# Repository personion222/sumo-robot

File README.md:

# sumo-robot
**Speedbump** - TEJ3MI sumo robot competition 2nd place winner.
- designed in OnShape and 3D printed
    <details>
    <summary>3D model screenshots</summary>

    </details><br>
- board designed in KiCad
    <details>
    <summary>schematic screenshots</summary>

    </details><br>
- powered by PIC16F15323 programmed with GCBasic script

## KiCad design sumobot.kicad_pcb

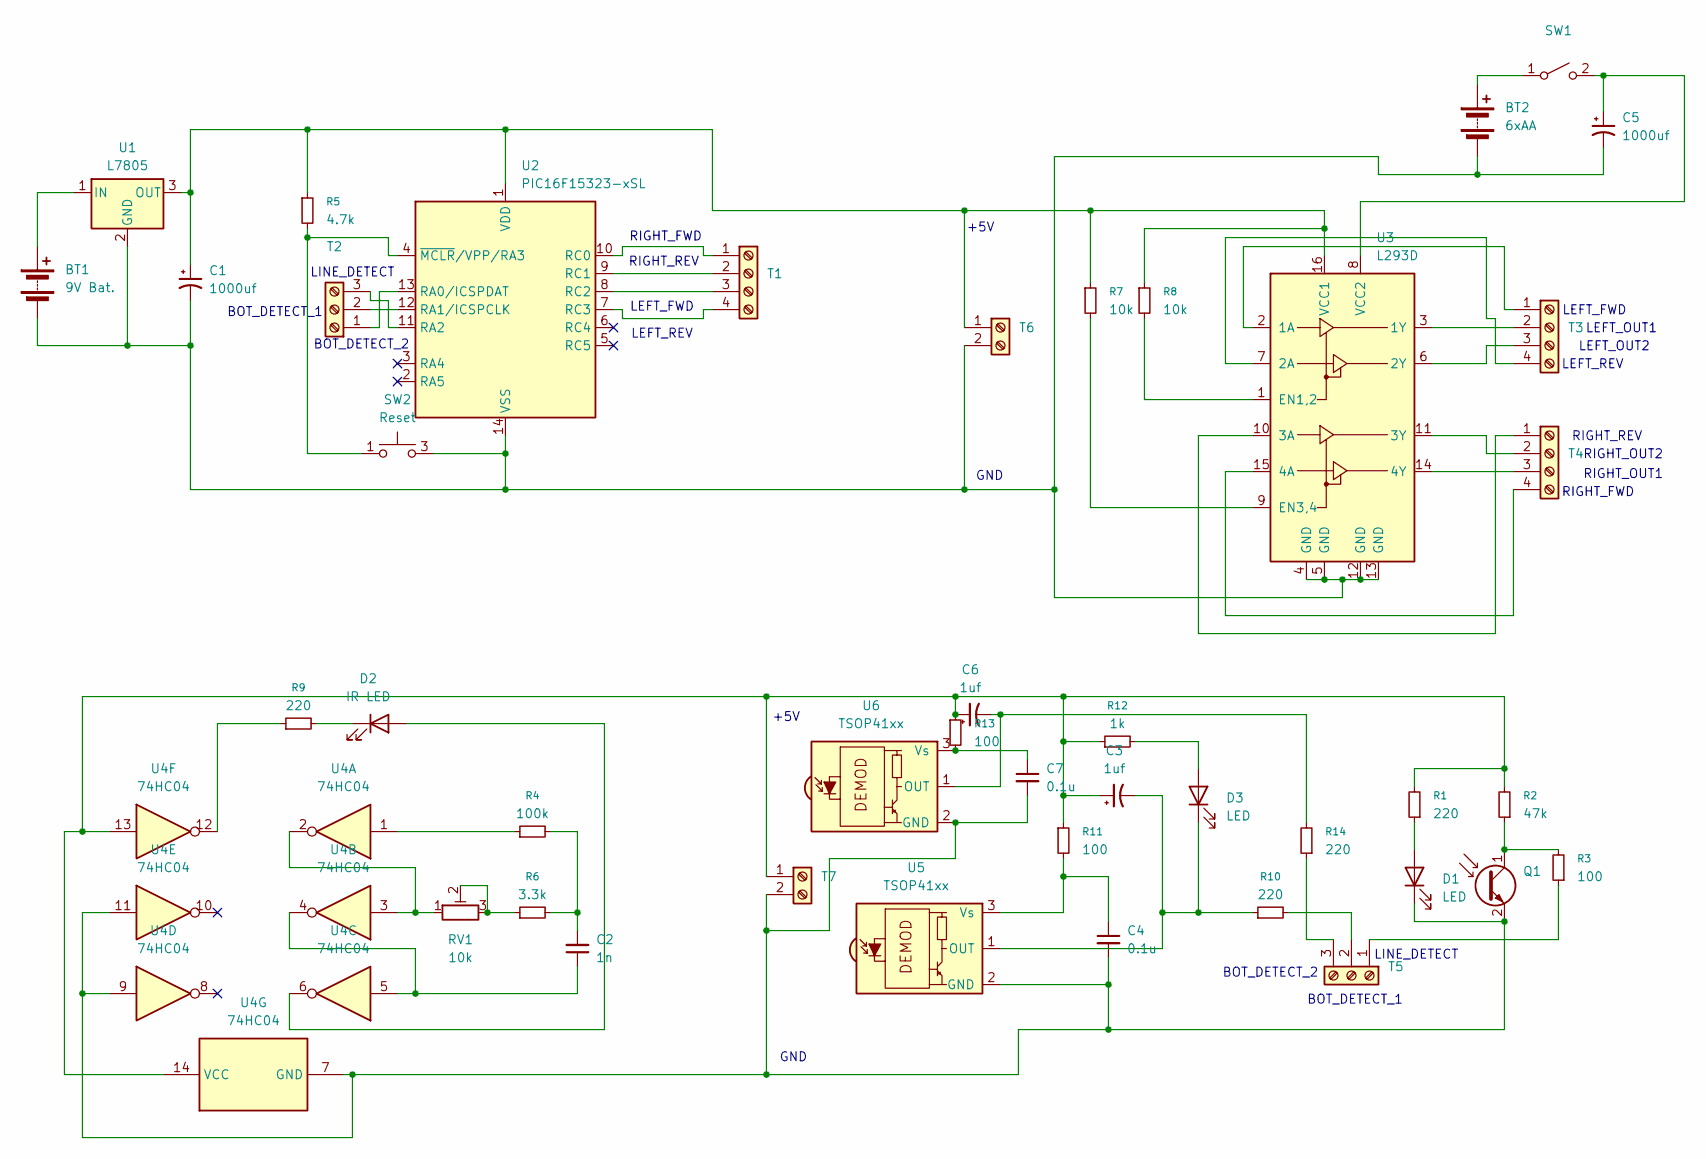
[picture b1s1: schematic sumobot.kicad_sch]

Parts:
BT1: 9V Bat.; TerminalBlock_MetzConnect_Type101_RT01602HBWC_1x02_P5.08mm_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
BT2: 6xAA; TerminalBlock_MetzConnect_Type101_RT01602HBWC_1x02_P5.08mm_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
C1, C5: 1000uf; CP_Radial_D10.0mm_P5.00mm
C2: 1n; C_Disc_D7.5mm_W2.5mm_P5.00mm
C3, C6: 1uf; C_Disc_D7.5mm_W2.5mm_P5.00mm
C4, C7: 0.1u; C_Disc_D7.5mm_W2.5mm_P5.00mm
D1, D3: LED; LED_D5.0mm_Clear
D2: IR LED; LED_D5.0mm_IRBlack
Q1: LED_D5.0mm_Clear
R1, R9, R10, R14: 220; R_Axial_DIN0207_L6.3mm_D2.5mm_P7.62mm_Horizontal
R2: 47k; R_Axial_DIN0207_L6.3mm_D2.5mm_P7.62mm_Horizontal
R3, R11, R13: 100; R_Axial_DIN0207_L6.3mm_D2.5mm_P7.62mm_Horizontal
R4: 100k; R_Axial_DIN0207_L6.3mm_D2.5mm_P7.62mm_Horizontal
R5: 4.7k; R_Axial_DIN0207_L6.3mm_D2.5mm_P7.62mm_Horizontal
R6: 3.3k; R_Axial_DIN0207_L6.3mm_D2.5mm_P7.62mm_Horizontal
R7, R8: 10k; R_Axial_DIN0207_L6.3mm_D2.5mm_P7.62mm_Horizontal
R12: 1k; R_Axial_DIN0207_L6.3mm_D2.5mm_P7.62mm_Horizontal
RV1: 10k; Potentiometer_Bourns_3386P_Vertical
SW1: SW_DIP_SPSTx01_Slide_9.78x4.72mm_W7.62mm_P2.54mm
SW2: Reset; SW_PUSH_1P1T_6x3.5mm_H5.0_APEM_MJTP1250
T1, T3, T4: TerminalBlock_MetzConnect_Type101_RT01604HBWC_1x04_P5.08mm_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
T2, T5: TerminalBlock_MetzConnect_Type101_RT01603HBWC_1x03_P5.08mm_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
T6, T7: TerminalBlock_MetzConnect_Type101_RT01602HBWC_1x02_P5.08mm_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
U1: L7805; TO-220-3_Vertical
U2: PIC16F15323-xSL; DIP-14_W7.62mm
U3: L293D; DIP-16_W7.62mm
U4: 74HC04; DIP-14_W7.62mm
U5, U6: TSOP41xx; Vishay_MOLD-3Pin

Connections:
unnamed: BT1.1 (+), U1.1 (IN)
unnamed: BT1.2 (-), BT2.2 (-), C1.2, C5.2, SW2.3 (B), SW2.4 (B), T6.2, U1.2 (GND), U2.14 (VSS), U3.4 (GND), U3.5 (GND), U3.12 (GND), U3.13 (GND)
unnamed: BT2.1 (+), SW1.1 (A)
unnamed: C2.1, U4.4, U4.5
unnamed: C2.2, R4.2, R6.2
unnamed: D1.2 (A), R1.1
unnamed: C4.2, C7.2, D1.1 (K), Q1.2 (E), T7.2, U4.7 (GND), U4.9, U4.11, U5.2 (GND), U6.2 (GND)
unnamed: D2.2 (A), U4.6
unnamed: D2.1 (K), R9.2
unnamed: D3.2 (A), R12.2
unnamed: C3.2, D3.1 (K), R10.1, U5.1 (OUT)
unnamed: Q1.1 (C), R2.1, R3.2
unnamed: R4.1, U4.1
unnamed: R6.1, RV1.2, RV1.3
unnamed: R9.1, U4.12
unnamed: RV1.1, U4.2, U4.3
unnamed: C5.1, SW1.2 (B), U3.8 (VCC2)
unnamed: T1.1, U2.10 (RC0)
unnamed: T1.2, U2.9 (RC1)
unnamed: T1.3, U2.8 (RC2)
unnamed: T1.4, U2.7 (RC3)
unnamed: T2.1, U2.13 (RA0/ICSPDAT)
unnamed: T2.2, U2.12 (RA1/ICSPCLK)
unnamed: T2.3, U2.11 (RA2)
unnamed: T3.1, U3.2 (1A)
unnamed: T3.2, U3.3 (1Y)
unnamed: T3.3, U3.6 (2Y)
unnamed: T3.4, U3.7 (2A)
unnamed: T4.1, U3.10 (3A)
unnamed: T4.2, U3.11 (3Y)
unnamed: T4.3, U3.14 (4Y)
unnamed: T4.4, U3.15 (4A)
unnamed: R3.1, T5.1
unnamed: R10.2, T5.2
unnamed: R14.1, T5.3
unnamed: C1.1, R5.1, R7.1, R8.1, T6.1, U1.3 (OUT), U2.1 (VDD), U3.16 (VCC1)
unnamed: C3.1, C6.1, R1.2, R2.2, R11.1, R12.1, R13.1, T7.1, U4.13, U4.14 (VCC)
unnamed: R5.2, SW2.1 (A), SW2.2 (A), U2.4 (~MCLR/VPP/RA3)
unnamed: R8.2, U3.1 (EN1,2)
unnamed: R7.2, U3.9 (EN3,4)
unnamed: C4.1, R11.2, U5.3 (Vs)
unnamed: C6.2, R14.2, U6.1 (OUT)
unnamed: C7.1, R13.2, U6.3 (Vs)

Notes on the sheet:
LINE_DETECT
BOT_DETECT_2
BOT_DETECT_1
RIGHT_REV
LEFT_FWD
LEFT_REV
LEFT_OUT1
RIGHT_FWD
GND
LEFT_OUT2
+5V
RIGHT_OUT2
RIGHT_OUT1
BOT_DETECT_2
BOT_DETECT_1

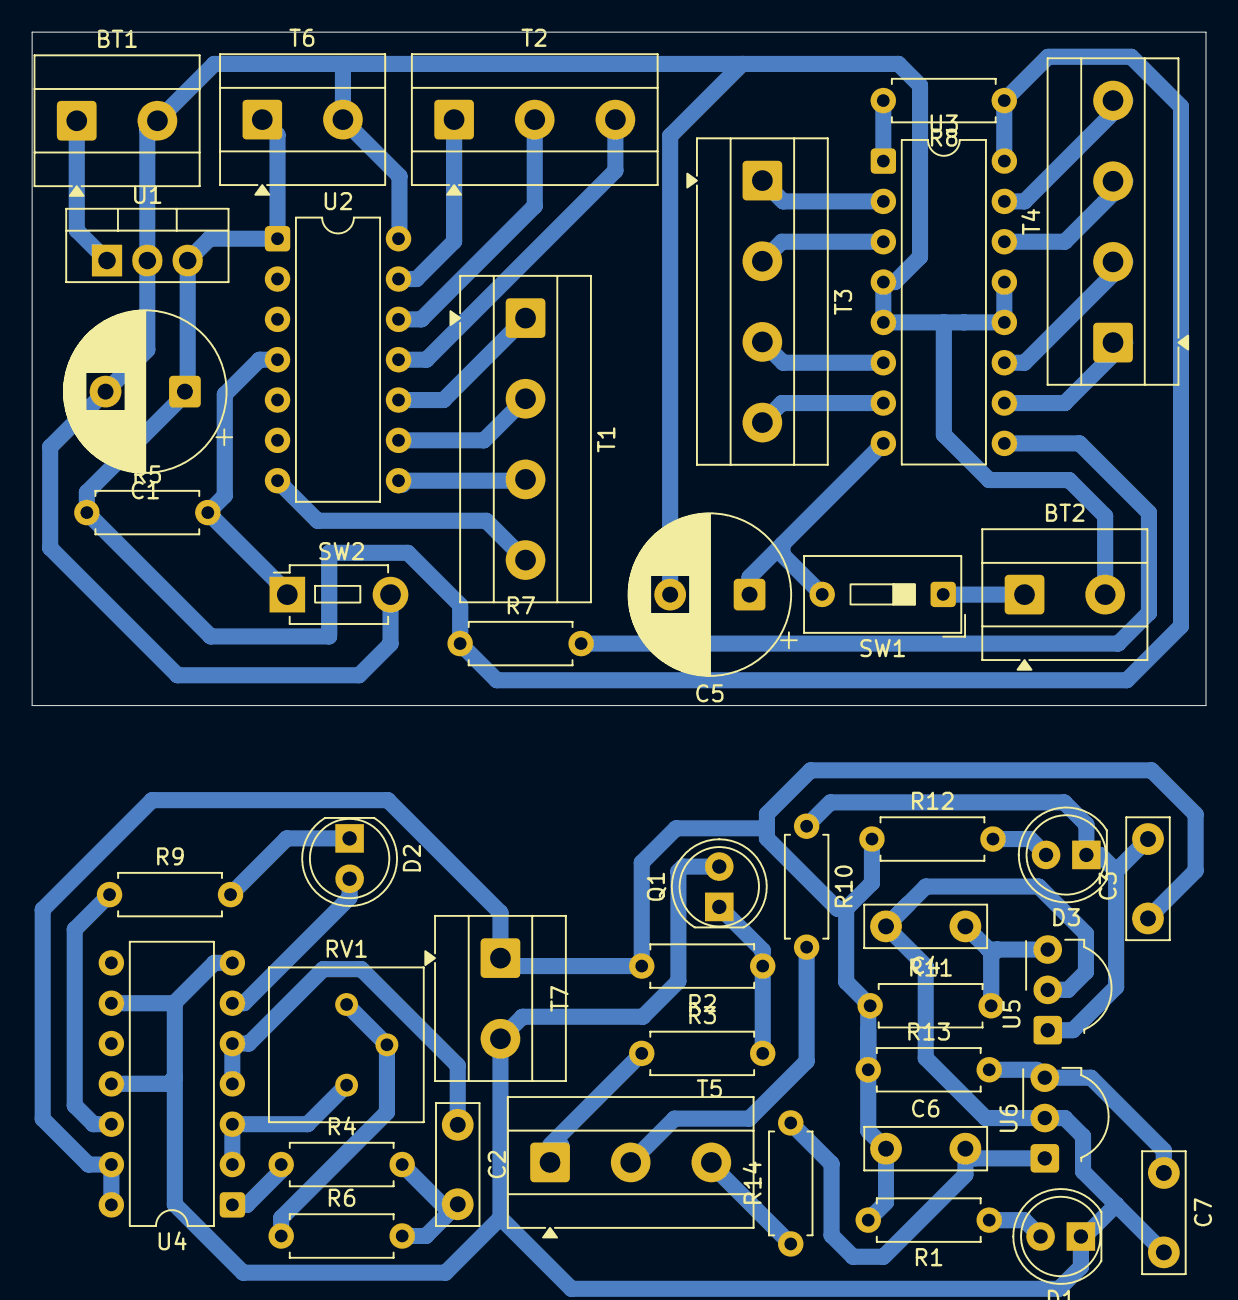
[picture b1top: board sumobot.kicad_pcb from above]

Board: 2 copper layers, 73.9 x 42.4 mm, 43 parts (0 on the bottom side), 43 nets.

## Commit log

2026-06-22 image stuffs
2026-06-22 readme updates + refactoring
2026-06-22 readme final for now
2026-06-24 minor changes
